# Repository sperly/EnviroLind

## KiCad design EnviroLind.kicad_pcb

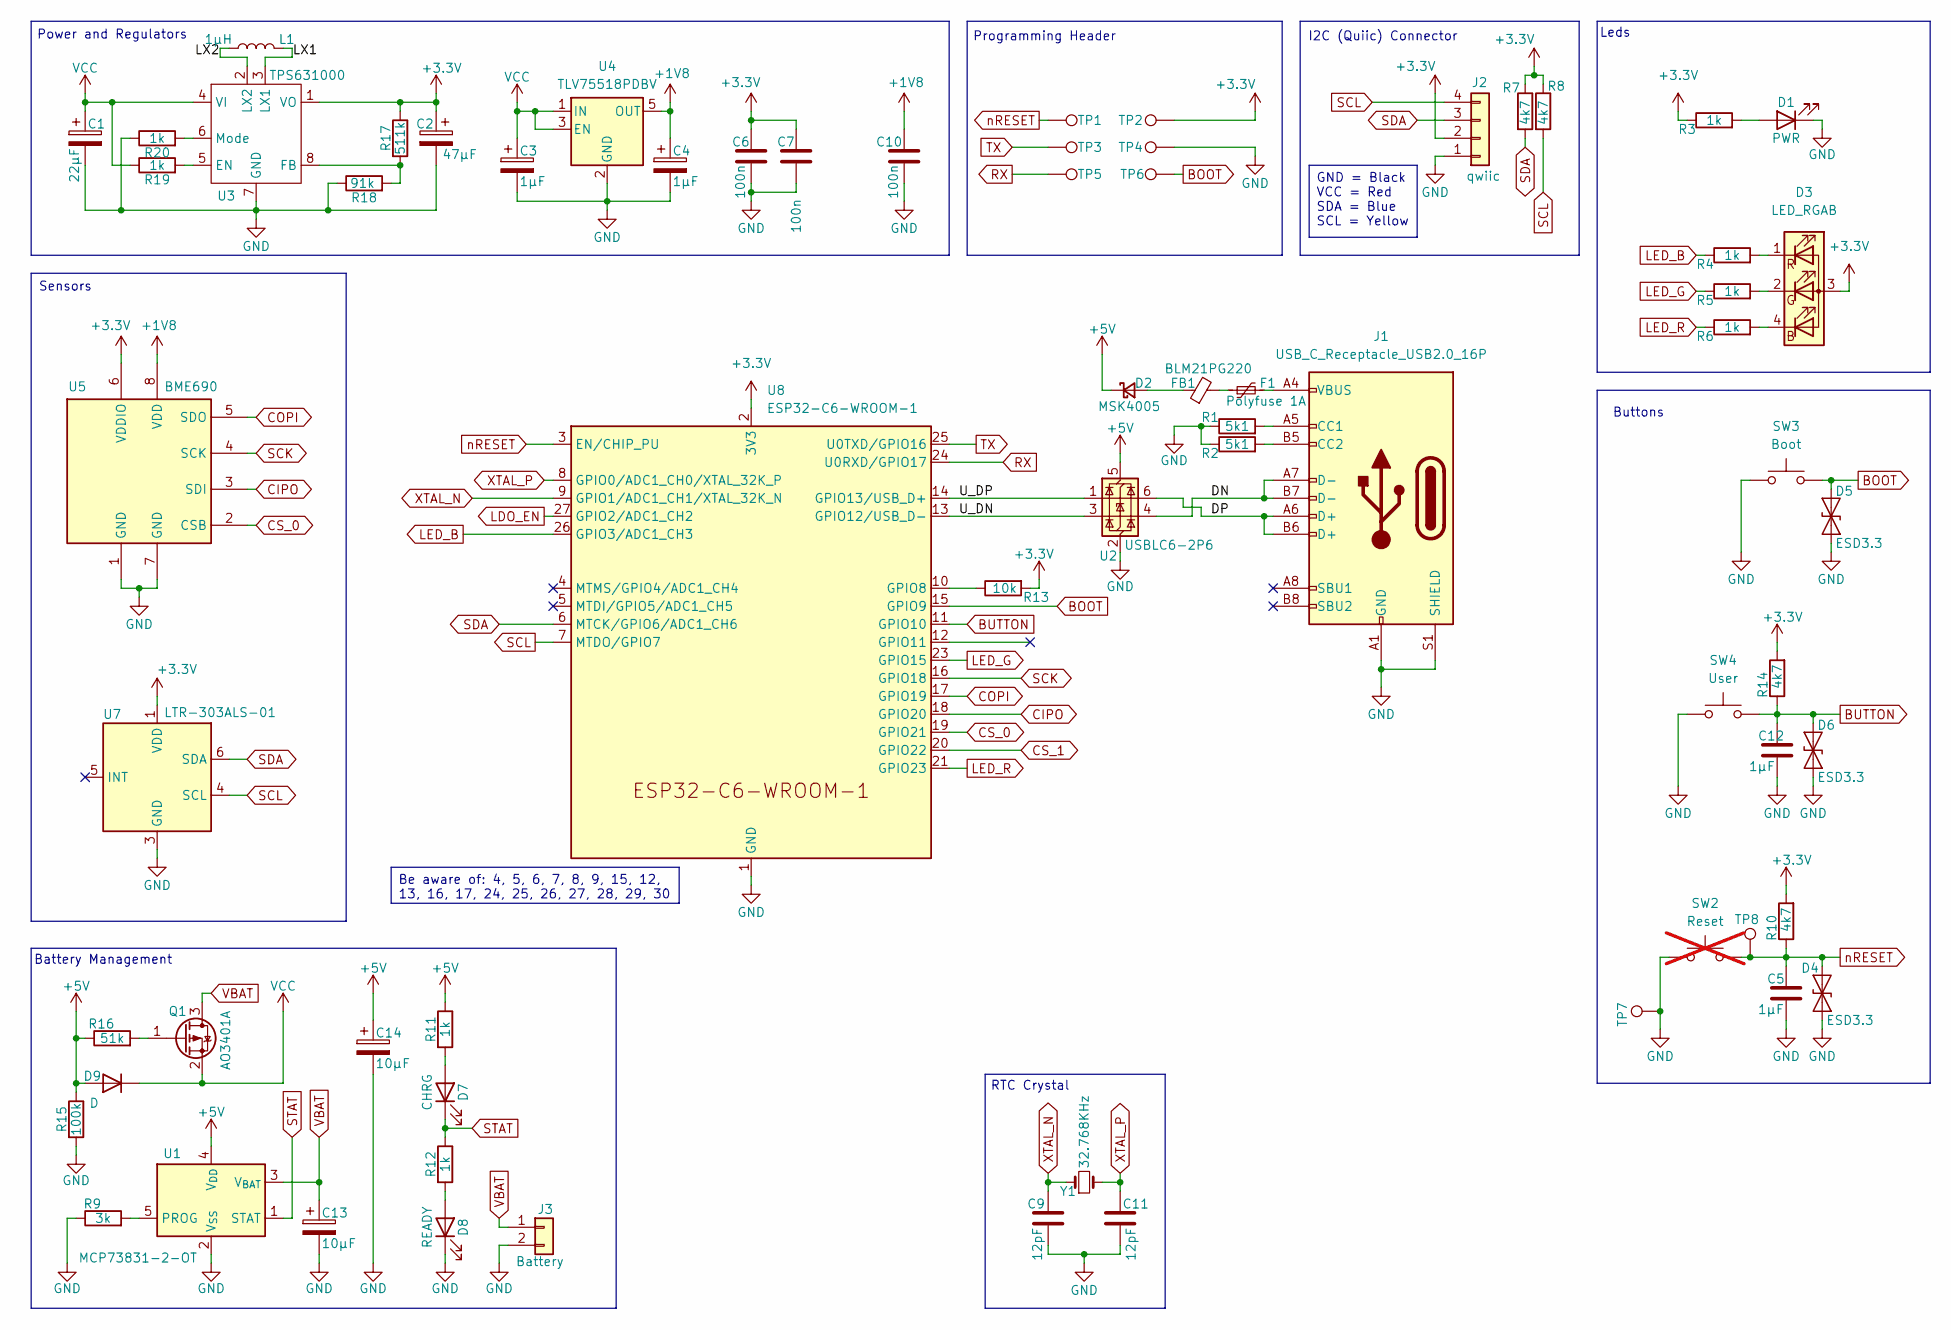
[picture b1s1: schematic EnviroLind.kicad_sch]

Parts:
C1: 22µF; C_0603_1608Metric
C2: 47µF; C_0603_1608Metric
C3, C4: 1µF; C_0603_1608Metric
C5, C12: 1µF; C_0402_1005Metric
C6, C7, C10: 100n; C_0402_1005Metric
C9, C11: 12pF; C_0402_1005Metric
C13, C14: 10µF; C_0603_1608Metric
D1: PWR; LED_0402_1005Metric
D2: MSK4005; D_SOD-523
D3: LED_RGAB; LED-RGB-CA-2012
D4, D5, D6: ESD3.3; D_SOD-923
D7: CHRG; LED_0402_1005Metric
D8: READY; LED_0402_1005Metric
D9: D; D_SOD-523
F1: Polyfuse 1A; C_0603_1608Metric
FB1: BLM21PG220; Fuse_0805_2012Metric
J1: USB_C_Receptacle_USB2.0_16P; USB_C_Receptacle_XKB_U262-16XN-4BVC11
J2: qwiic; JST_SH_SM04B-SRSS-TB_1x04-1MP_P1.00mm_Horizontal
J3: Battery; JST_PH_S2B-PH-K_1x02_P2.00mm_Horizontal
L1: 1µH; L_0805_2012Metric
Q1: AO3401A; SOT-23
R1, R2: 5k1; R_0402_1005Metric
R3, R4, R5, R6, R11, R12, R19, R20: 1k; R_0402_1005Metric
R7, R8, R10, R14: 4k7; R_0402_1005Metric
R9: 3k; R_0402_1005Metric
R13: 10k; R_0402_1005Metric
R15: 100k; R_0402_1005Metric
R16: 51k; R_0402_1005Metric
R17: 511k; R_0402_1005Metric
R18: 91k; R_0402_1005Metric
SW2: Reset; Panasonic_EVQPUJ_EVQPUA; not fitted
SW3: Boot; Panasonic_EVQPUJ_EVQPUA
SW4: User; Panasonic_EVQPUJ_EVQPUA
TP1: RST; TestPoint_Pad_D1.0mm
TP2: VCC; TestPoint_Pad_D1.0mm
TP3: TX; TestPoint_Pad_D1.0mm
TP4: GND; TestPoint_Pad_D1.0mm
TP5: RX; TestPoint_Pad_D1.0mm
TP6, TP7, TP8: BOOT; TestPoint_Pad_D1.0mm
U1: MCP73831-2-OT; SOT-23-5
U2: USBLC6-2P6; SOT-666
U3: TPS631000; SOT-583-8
U4: TLV75518PDBV; SOT-23-5
U5: BME690; Bosch_LGA-8_2.5x2.5mm_P0.65mm_ClockwisePinNumbering
U7: LTR-303ALS-01; Lite-On_LTR-303ALS-01
U8: ESP32-C6-WROOM-1
Y1: 32.768KHz; Crystal_SMD_3215-2Pin_3.2x1.5mm

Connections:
+1V2: C4.1, C10.1, U4.5 (OUT), U5.8 (VDD); also elsewhere on the board
+3.3V: C2.1, C6.1, C7.1, D3.3 (A), J2.2, R3.1, R7.1, R8.1, R10.2, R13.2, R14.2, R17.1, TP2.1, U3.1 (VO), U5.6 (VDDIO), U7.1 (VDD), U8.2 (3V3); also elsewhere on the board
+5V: C14.1, D2.1 (K), D9.2 (A), R11.1, R15.1, R16.1, U1.4 (V_{DD}), U2.5 (VBUS)
/DN: J1.A7 (D-), J1.B7 (D-), U2.4 (I/O2)
/DP: J1.A6 (D+), J1.B6 (D+), U2.6 (I/O1)
/LX1: L1.2, U3.3 (LX1)
/LX2: L1.1, U3.2 (LX2)
/U_DN: U2.3 (I/O2), U8.13 (GPIO12/USB_D-)
/U_DP: U2.1 (I/O1), U8.14 (GPIO13/USB_D+)
BOOT: D5.2 (A2), SW3.2, TP6.1, U8.15 (GPIO9)
BUTTON: C12.1, D6.2 (A2), R14.1, SW4.2, U8.11 (GPIO10)
CIPO: U5.3 (SDI), U8.18 (GPIO20); also elsewhere on the board
COPI: U5.5 (SDO), U8.17 (GPIO19); also elsewhere on the board
CS_0: U5.2 (CSB), U8.19 (GPIO21)
CS_1: U8.20 (GPIO22); also elsewhere on the board
GND: C1.2, C2.2, C3.2, C4.2, C5.2, C6.2, C7.2, C9.2, C10.2, C11.2, C12.2, C13.2, C14.2, D1.1 (K), D4.1 (A1), D5.1 (A1), D6.1 (A1), D8.1 (K), J1.A1 (GND), J1.A12 (GND), J1.B1 (GND), J1.B12 (GND), J1.S1 (SHIELD), J2.1, J3.2, R1.1, R2.1, R9.1, R15.2, R18.1, R20.1, SW2.1, SW3.1, SW4.1, TP4.1, TP7.1, U1.2 (V_{SS}), U2.2 (GND), U3.7 (GND), U4.2 (GND), U5.1 (GND), U5.7 (GND), U7.3 (GND), U8.1 (GND), U8.28 (GND), U8.29 (GND); also elsewhere on the board
LED_B: R4.1, U8.26 (GPIO3/ADC1_CH3)
LED_G: R5.1, U8.23 (GPIO15)
LED_R: R6.1, U8.21 (GPIO23)
unnamed: D1.2 (A), R3.2
unnamed: D2.2 (A), FB1.1
unnamed: D3.4 (BK), R6.2
unnamed: D3.2 (GK), R5.2
unnamed: D3.1 (RK), R4.2
unnamed: D7.2 (A), R11.2
unnamed: D8.2 (A), R12.2
unnamed: F1.1, FB1.2
unnamed: F1.2, J1.A4 (VBUS), J1.A9 (VBUS), J1.B4 (VBUS), J1.B9 (VBUS)
unnamed: J1.A5 (CC1), R1.2
unnamed: J1.B5 (CC2), R2.2
unnamed: Q1.1 (G), R16.2
unnamed: R9.2, U1.5 (PROG)
unnamed: R19.2, U3.5 (EN)
unnamed: R17.2, R18.2, U3.8 (FB)
unnamed: R20.2, U3.6 (Mode)
unnamed: R13.1, U8.10 (GPIO8)
RX: TP5.1, U8.24 (U0RXD/GPIO17)
SCK: U5.4 (SCK), U8.16 (GPIO18); also elsewhere on the board
SCL: J2.4, R8.2, U7.4 (SCL), U8.7 (MTDO/GPIO7)
SDA: J2.3, R7.2, U7.6 (SDA), U8.6 (MTCK/GPIO6/ADC1_CH6)
STAT: D7.1 (K), R12.1, U1.1 (STAT)
TX: TP3.1, U8.25 (U0TXD/GPIO16)
VBAT: C13.1, J3.1, Q1.3 (D), U1.3 (V_{BAT})
XTAL_N: C9.1, U8.9 (GPIO1/ADC1_CH1/XTAL_32K_N), Y1.1
XTAL_P: C11.1, U8.8 (GPIO0/ADC1_CH0/XTAL_32K_P), Y1.2
nRESET: C5.1, D4.2 (A2), R10.1, SW2.2, TP1.1, TP8.1, U8.3 (EN/CHIP_PU)

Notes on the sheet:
Programming Header
RTC Crystal
Leds
I2C (Quiic) Connector
Battery Management
Buttons
Power and Regulators
Sensors
Be aware of: 4, 5, 6, 7, 8, 9, 15, 12, 13, 16, 17, 24, 25, 26, 27, 28, 29, 30
GND = Black VCC = Red SDA = Blue SCL = Yellow

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
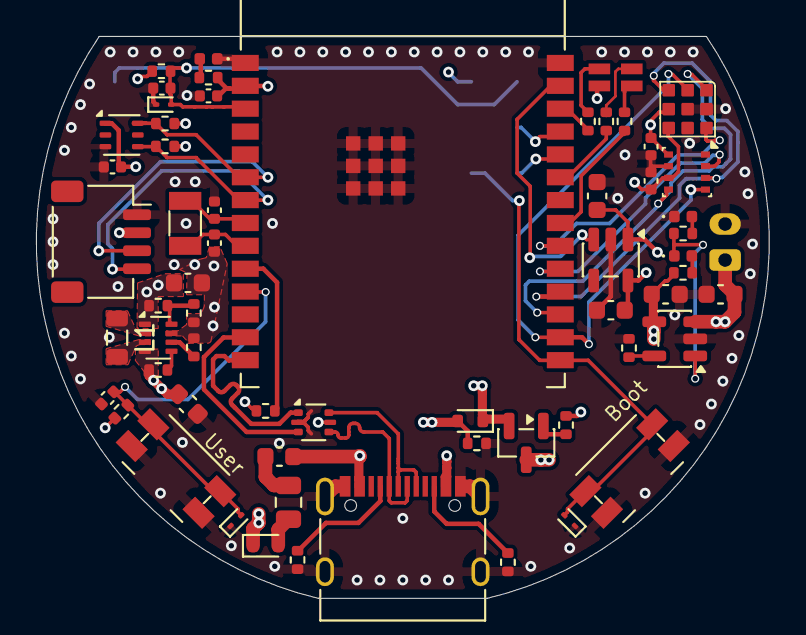
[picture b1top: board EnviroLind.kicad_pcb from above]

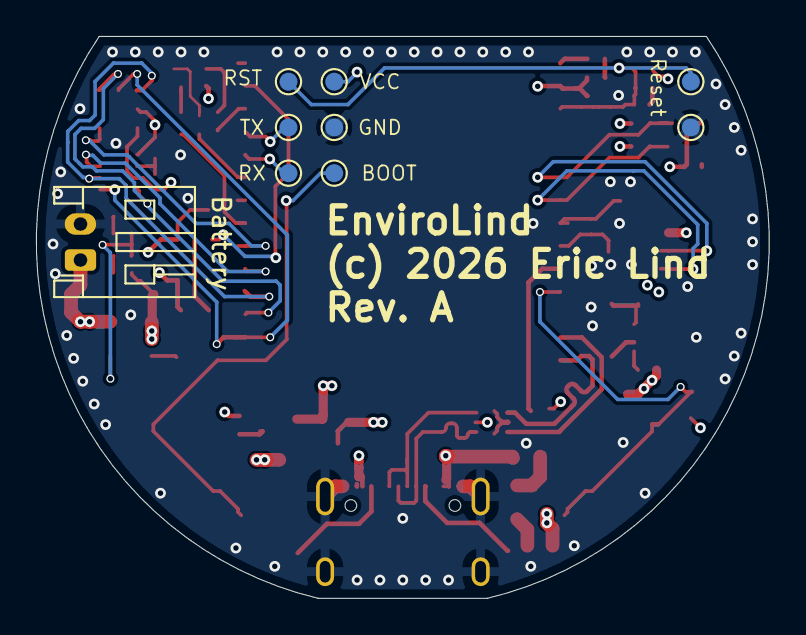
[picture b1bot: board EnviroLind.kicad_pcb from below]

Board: 4 copper layers, 40.7 x 31.2 mm, 69 parts (9 on the bottom side), 48 nets.

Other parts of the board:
C8: 100n; C_0402_1005Metric
U6: ENS161; LGA9

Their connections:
+1V2: U6.4 (VDD); also elsewhere on the board
+3.3V: C8.1, U6.5 (VDDIO); also elsewhere on the board
CIPO: U6.3 (CIPO/ADDR); also elsewhere on the board
COPI: U6.1 (COPI/SDA); also elsewhere on the board
CS_1: U6.7 (nCS); also elsewhere on the board
GND: C8.2, U6.8 (GND), U6.9 (GND); also elsewhere on the board
SCK: U6.2 (SCK/SCL); also elsewhere on the board

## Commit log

2026-01-07 Initial commit, first revision
2026-01-13 Start of power rework
2026-01-18 Before resize

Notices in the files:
EnviroLind.kicad_pcb:
(c) 2026 Eric Lind
